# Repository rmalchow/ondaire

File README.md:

# ondaire

**Self-organizing multiroom audio.** One small binary per device. Start it on
two machines and they find each other, form a group, and play the same music
in sync — no server, no database, no config files, no cloud.

```
┌── kitchen ──┐   ┌── living room ──┐   ┌── bedroom ──┐
│  ondaire   │◀─▶│    ondaire     │◀─▶│  ondaire   │
└─────────────┘   └────────┬────────┘   └─────────────┘
                           │ plays a track from its library,
                           ▼ streams it in lock-step to the whole group
                     🔊  🔊  🔊   one song, every room, in time
```

- **Zero-config** — nodes discover each other over mDNS + gossip and replicate
  their state automatically. Pull the plug on any node and the rest heal.
- **One universal binary** — no cgo, no build flavors. Opus and ALSA are loaded
  at runtime if present, so the same `linux/amd64` or `linux/arm64` build runs
  on a beefy desktop or a Raspberry Pi.
- **Synchronized playback** — a master-anchored clock plus a per-node rate servo
  keep rooms aligned; lost packets are recovered with FEC or TCP.
- **Built-in web UI** — every node serves a single-page app at `/`. Control the
  whole cluster from any one of them.
- **Plays your stuff** — local files (`wav` / `mp3` / `flac`), internet radio
  (`http(s)://…`), or a line-in capture. Browse any node's library from any UI.
- **Group as you like** — any node is a group of one by default; tell one to
  follow another and they merge. Name a combination of rooms and the name
  sticks whenever that set reforms.

> A node can also be a receive-only **player**: the wire protocol is small and
> documented in [`docs/developer/player-protocol.md`](docs/developer/player-protocol.md) for firmware
> (e.g. an ESP32 + DAC), with a reference player in [`cmd/player`](cmd/player).

---

## Quick start

### Build

Needs Go 1.26 and Node (for the UI). Pure-Go, statically-ish linked:

```sh
git clone https://gitlab.rand0m.me/share/ondaire.git
cd ondaire
./scripts/build.sh --ui     # builds the SPA, then linux amd64 + arm64 into bin/,
                            # plus ./ondaire for this host
```

Prebuilt binaries are attached to each [tagged release](RELEASING.md).

**Running in Docker?** A multi-arch master image (amd64 + arm64, Spotify Connect
built in) plus a Compose example live in [`docker/`](docker/) — see the
[Docker quick start](QUICKSTART.md).

### Run

On each device:

```sh
./ondaire
```

That's it — defaults are sensible. The node mints a permanent ID on first run,
binds its ports, advertises itself over mDNS, and starts serving the UI. Run it
on a second machine on the same LAN and they find each other within seconds.

Open the UI in a browser:

```
http://<that-device's-ip>:8080
```

Put music in the node's library directory (created on first run):

```
<data-dir>/media/        # default: ./data/media — folders are browsed recursively
```

### Two nodes on one machine (to try it out)

```sh
./scripts/dev2.sh        # launches two nodes on 127.0.0.1 with null audio sinks
```

…or run the full end-to-end smoke test:

```sh
./scripts/e2e.sh
```

---

## Using the UI

Every node serves the same app and proxies to the others, so open
`http://<any-node-ip>:8080` on a phone or browser. There are two pages: the
**Rooms** overview (landing page) and the **Nodes** page (the **⚙ gear**,
top-right).

- **Rooms** — one card per group: now-playing (cover art / title / artist),
  group + per-member volumes, and — when you select a card — the add-players
  roster, the media browser, and advanced per-group settings (codec/transport/
  buffer).
- **Nodes** — per-node cards: addresses, feature toggles (playback/opus/input,
  plus a **spotify** badge), **Spotify endpoints** (Connect devices + presets),
  and settings (volume, hw delay, output device, test tone).

📖 **Full walkthrough with screenshots: [docs/user](docs/user/README.md).**

---

## Configuration

Flags (each has an `ONDAIRE_*` env equivalent); all are optional:

| Flag | Default | What |
|------|---------|------|
| `--data <dir>` | `./data` | data dir: `node.json`, `cluster.json`, `media/` |
| `--media <dir>` | `<data>/media` | library directory (browsed recursively) |
| `--name <name>` | first 8 of the node ID | display name (first start only) |
| `--http-port` | `8080` | UI + REST API + WebSocket + node proxy |
| `--stream-port` | `9090` | member-side stream + clock sync (tcp+udp) |
| `--source-port` | `9200` | audio source: subscriptions + control (tcp+udp) |
| `--gossip-port` | `7946` | cluster gossip (tcp+udp) |
| `--host <addr>` | all interfaces | bind address |
| `--output <spec>` | `auto` | output backend: `auto` \| `alsa` \| `exec` \| `null` \| `file:<path>` |

Ports are **bind-or-increment** *when left at the default*: if one is taken the
node tries the next and advertises whatever it actually bound. A port you **set
explicitly** (flag or `ONDAIRE_*_PORT` env) is **pinned** — it binds that exact
number or the node exits with a clear error, so a misconfiguration surfaces
immediately instead of silently drifting.

Env-only knobs:

| Env | Default | What |
|-----|---------|------|
| `ONDAIRE_ALSA_LATENCY_MS` | `200` | ALSA device buffer (raise on a glitchy Pi) |
| `ONDAIRE_LOG` | `info` | log level (`debug` \| `info` \| `warn` \| `error`) |

`auto` picks the best available backend: **alsa → exec** (`pw-play`/`aplay`/…)
**→ null**. Pass `-v` for debug logging; `ondaire run …` is accepted as an
alias for `ondaire …`.

For a hermetic setup without mDNS (e.g. tests, or a segmented network), use
`--no-mdns` with `--join <host:gossipPort>,…` seeds.

---

## How it works (in one breath)

Every node runs the identical binary and is, by default, the master of a group
containing only itself. Telling node B to *follow* node A merges them; the only
replicated fact is each node's `following` field — group membership, the group
ID (the master's ID), and failover all fall out of that, recomputed everywhere
from gossiped state. When a group plays, its master opens the media source,
stamps each 20 ms PCM/Opus frame with a presentation time on the shared clock,
and streams it to every member (including itself) that has *subscribed* to its
source port. Each member runs a clock follower and a jitter-buffered, rate-
servo'd playout so the audio leaves every speaker at the same instant.

Deeper docs live in [`docs/`](docs/), organized into four groups: the
[user guide](docs/user/), the [architecture reference](docs/architecture/)
(topic pages — wire protocol, clock sync, playout pipeline, sequence diagrams, …),
the [developer docs](docs/developer/) (the [player wire protocol](docs/developer/player-protocol.md),
the [ESP32 hardware node](docs/developer/esp32.md), and
[acoustic calibration](docs/developer/calibration.md)), and a
[reference section](docs/reference/) of external prior art.
[`RELEASING.md`](RELEASING.md) covers releases.

## Measured coherence

Sync is easy to claim, so we measured it. With a single USB microphone in the
room and two Raspberry-Pi players (`pi01` → left, `pi02` → right) we recorded the
real acoustic gap between the speakers over a 12-minute run.

**How it's measured.** Each speaker plays a wideband log-sine sweep, time-
interleaved L/R so the two never overlap. The recording is matched-filtered
against the reference sweep with sub-sample parabolic interpolation to pin each
arrival. The trick that makes it robust: every `pi02` sweep is referenced to the
**midpoint of its two bracketing `pi01` sweeps**, which cancels the (large,
common) playback-vs-microphone clock rate exactly and leaves only the
`pi01`↔`pi02` offset. As a ground-truth check, a deliberate ~50 cm speaker move
was recovered as 46 cm from the audio alone. The toolkit is pure Python in
[`tools/calib/`](tools/calib/) (`lr_drift.py`, `compare_drift.py`); the full
write-up is in [`docs/developer/calibration.md`](docs/developer/calibration.md).

### Inter-speaker offset: 716 µs RMS

The two speakers held to **716 µs RMS**, peak-to-peak ~2.7 ms. The curve is a
smooth thermal "bowl" (sound-card crystals warming up), not fast jitter. The
precedence/Haas effect fuses two arrivals into one perceived source up to ~5–10
ms, so this stays well inside the single-source range — sub-millisecond most of
the session, with a slow multi-ms thermal excursion the rate-servo doesn't cancel.

### What the servo can't see

Polling the master's per-node STATUS telemetry (`GET /api/playback/statuses`)
during the same run, the players' self-reported clock-offset difference stays
nearly flat while the microphone sees the full ~2.7 ms wander — correlation
**r = +0.20**. The drift lives **downstream of the clock the servo controls**, in
the DAC/analog path, where the chain is currently blind to it. That gap is small
enough to be inaudible, but it's exactly what on-demand acoustic calibration
(`outputDelayMs`) is designed to measure and null.

## Status & scope

Works today: discovery, grouping, takeover, synchronized playback, pause/resume,
opus, per-node volume/delay/device, persisted names & settings, the web UI, and
a tag-driven release pipeline. Out of scope for now: auth/TLS, internet-facing
operation, playlists, and hardware-mixer volume. v1 is a trusted-LAN system.

## On AI

Yes — I used Claude for much of this code. No, it isn't vibe-coded AI slop. The
architecture, the clock-sync math, the wire protocol, and the trade-offs behind
every design decision are my own thinking and experience, and I know and
understand pretty much every line that ships. I used AI the way you'd use any
good power tool: to get past my own laziness and move faster, not to outsource
the judgement. If something in here is wrong, that's on me, not on a model.

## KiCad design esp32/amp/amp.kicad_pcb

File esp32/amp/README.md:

# ondaire amp — ESP32-S3 carrier / 50 W class-D node

A KiCad 10 project for a **powered-speaker node**: an ESP32-S3 dev board drops
into a socket, an I²S DAC + class-D amp turn the stream into ~40–50 W of audio,
and the whole thing runs from a single USB-C cable via USB-PD. JST plugs bring
out a rotary encoder and an I²C OLED.

This carrier is the hardware counterpart to the `esp32/` firmware in this repo —
the GPIO map, I²S pins and encoder pins are taken straight from
`esp32/boards/board_esp32s3_*.h`, so a flashed Super Mini or Waveshare Zero
works with no reconfiguration.

> **Status — schematic ERC-clean; board placed + ground-poured, not yet routed.**
> Schematic, symbols, footprints, BOM and netlist are generated and validated
> (`kicad-cli sch erc` → 0 errors). The `.kicad_pcb` has every footprint placed
> in a functional floorplan with GND zones on both layers; DRC is clean except
> the expected unrouted ratsnest (no overlaps/clearance/short errors). **Signal
> and power routing is the remaining manual step.** A few values need a
> datasheet/board check before you order — see
> [Verify before you order](#verify-before-you-order).

---

## Block diagram

```
            ┌───────── USB-C (PD) ─────────┐
   charger  │  VBUS ─┬─────────────► +20V rail ──────────────┐
   ─────────┤  CC1/2─┤ CH224K       (≈3 A @ 20 V)            │
   20V/65W+ │  D±  ───┘ PD sink                              │
            └─────────┘  (CFG1: NC = request 20 V)           │
                                                             │
          +20V ──► LM2596S-5.0 buck ──► +5V ──► AMS1117-3.3 ──► +3V3
                                         │                      │
                                         ▼                      ▼
                                   ESP32-S3 socket        PCM5102A DAC
                                   (Super Mini / Zero)    (MCLK-less I²S)
                                         │  I²S BCK/LRCK/DIN     │
                                         └──────────────────────┘
                                                                │ OUT L/R
                                       L+R passive sum ◄─────────┘
                                                │
                          +20V ──► TPA3116D2 (PBTL mono) ──► LC filter ──► SPEAKER
                                       ▲   ▲                              (4 Ω, ~50 W)
                                  SD/FAULT  gain=20 dB
                                       │
   JST: OLED (I²C SDA/SCL) ────────────┤ ESP32 GPIO
   JST: rotary encoder (A/B/SW) ───────┘
```

## What was decided

| Choice | Decision | Why |
|---|---|---|
| Amp topology | **TPA3116D2, mono PBTL** | One speaker per node; PBTL gives ~40–50 W into 4 Ω from a 20 V rail (min load 1.6 Ω). |
| DAC | **PCM5102A**, MCLK-less | Matches the firmware (`i2s_mclk = -1`, internal PLL); clean 2.1 Vrms line out, no I²C config. |
| Power | **USB-PD 20 V via CH224K** | Single-cable power; 20 V is the TPA3116's sweet spot. Single-resistor select, default = 20 V. |
| ESP socket | **Both Super Mini + Zero** | Populate one footprint; identical nets, so one board fits either dev board. |
| Buck / LDO | LM2596S-5.0 → AMS1117-3.3 | 20 V is above most synchronous bucks' input max; LM2596 (40 V in) is robust. Separate clean 3V3 for the DAC. |

## Signal & power chain (the important bits)

**USB-PD (CH224K).** USB-C VBUS feeds the +20 V rail directly; the CH224K only
negotiates. Voltage is set in *single-resistor* mode: **R1 on CFG1→GND, with
CFG2/CFG3 unconnected.** R1 **unpopulated = 20 V**; 6.8 k = 9 V, 24 k = 12 V,
56 k = 15 V (WCH CH224K DS §5.2.1). D± route to the CH224K for BC1.2 fallback.

**Amp (TPA3116D2 PBTL).** Wired per the TI datasheet mono mode (SLOS708G §7.4.1,
Fig. 36):
- `LINP`, `LINN` → GND (this selects PBTL/mono at power-up).
- Signal into `RINP`/`RINN` (single-ended L+R sum, AC-coupled).
- Outputs paralleled: **`OUTPR ∥ OUTNR` → SPK+**, **`OUTPL ∥ OUTNL` → SPK−**,
  each half-bridge through its own 10 µH inductor, 1 µF across the speaker
  (PBTL filter, min L = 10 µH / C = 1 µF).
- `MODSEL` = GND (BD modulation, lowest THD with the LC filter).
- `PLIMIT` tied to `GVDD` (no power limit). `GAIN/SLV` = 5.6 k to GVDD → **20 dB,
  master mode** (lowest gain the part offers).
- `SDZ` (enable) ← ESP GPIO1 with a 100 k pull-down (amp stays off at boot).
  `FAULTZ` → GPIO4 (10 k pull-up). `MUTE` tied low (software volume handles mute).
- All four `BSxx` bootstrap caps = 220 nF. `AVCC` fed from +20 V through a 3.3 Ω
  RC. PowerPAD → GND (thermal vias).

**Gain / headroom.** At 20 dB the PCM5102A's 2.1 Vrms full-scale over-drives the
20 V rail by a few dB, so the **firmware's digital volume sets the real level** —
keep it below ~−4 dBFS for clean full power (normal listening is well under that).
To hard-limit in hardware, populate **R17** (MIXIN→GND, DNP) to attenuate/divide
the summer.

## GPIO map (matches `esp32/boards/board_esp32s3_*.h`)

| Signal | GPIO | Notes |
|---|---|---|
| I²S BCK | 5 | → PCM5102A BCK |
| I²S LRCK | 6 | → PCM5102A LCK |
| I²S DIN | 7 | → PCM5102A DIN (MCLK-less; SCK→GND) |
| Encoder A / B / SW | 15 / 16 / 17 | KY-040 / EC11 via JST (J4) |
| I²C SDA / SCL | 8 / 18 | SSD1306 OLED via JST (J3) |
| Amp enable (SDZ) | 1 | **new** — drive high to un-shutdown the amp |
| CH224K PG | 2 | **new** — power-good input |
| Amp FAULTZ | 4 | **new** — fault input (open-drain) |

GPIO 1/2/4/8/18 are the carrier-only additions; they're free and conflict-free on
both boards. The firmware doesn't drive amp-enable / fault / OLED yet — the board
is forward-looking on those. (3V3 from the dev board is left unconnected; the
carrier makes its own clean 3V3 for the DAC.)

## Power budget

| Rail | Source | Load | Worst-case |
|---|---|---|---|
| +20 V | USB-PD | TPA3116 PVCC | ~3 A at full output |
| +5 V | LM2596S-5.0 | ESP32 (Wi-Fi TX peaks) + LDO | ~1 A |
| +3V3 | AMS1117-3.3 | DAC + OLED + pull-ups | ~50 mA |

Full output (~50 W audio, ~90 % amp efficiency) + logic ≈ **60 W** → use a
**≥ 65 W (20 V / 3.25 A) charger**; a 100 W (20 V/5 A) supply gives headroom.
A 60 W (20 V/3 A) charger works but limits peak SPL.

## Files

| File | What |
|---|---|
| `amp.kicad_pro` | Project. Open this in KiCad 10. |
| `amp.kicad_sch` | Schematic (generated). |
| `amp.kicad_pcb` | Board: placed + GND-poured, unrouted (generated). |
| `amp.kicad_sym` | Project symbols: TPA3116D2 + the two ESP32 sockets (generated). |
| `amp.pretty/` | Project footprints: ESP32 dev-board sockets (generated, **placeholder geometry**). |
| `sym-lib-table`, `fp-lib-table` | Register the `amp` libs for this project. |
| `bom.csv` | Grouped BOM with LCSC starting points (generated). |
| `gen_*.py`, `ksym.py` | The generators — **edit these, not the outputs.** |

### Regenerating

The schematic/symbols/footprints/BOM are produced from declarative data so the
design is diffable and editable. After changing `gen_sch.py` (netlist/parts):

```sh
cd esp32/amp
python3 gen_symbols.py      # amp.kicad_sym
python3 gen_footprints.py   # amp.pretty/*
python3 gen_sch.py          # amp.kicad_sch
python3 gen_bom.py          # bom.csv
python3 gen_pcb.py          # amp.kicad_pcb (needs KiCad's pcbnew python module)
kicad-cli sch erc amp.kicad_sch   # validate schematic
kicad-cli pcb drc amp.kicad_pcb   # validate board
```

The schematic is a **connectivity-capture** style: components on a grid with a
global label on every pin (same name = same net). It's ERC-clean and exports a
correct netlist; tidy the layout/wiring in Eeschema if you want a pretty sheet.

## PCB layout

`gen_pcb.py` builds the board with the `pcbnew` API: it reads each footprint's
real courtyard size and shelf-packs the parts into functional regions (power-in
+ PD top-left, buck/LDO across the top, DAC upper-right, amp + output filter +
speaker lower-right, sockets + user-IO on the left), then pours **GND on both
copper layers**. The TPA3116 uses the `_ThermalVias` footprint, so its PowerPAD
is already stitched to the back plane.

What's left for you (in Pcbnew):

1. **Fill zones** — they're saved unfilled (a headless-`pcbnew` limitation);
   press `B` or *Edit → Fill All Zones* on open. This connects the whole GND net.
2. **Route** the ~46 non-GND nets. Suggested priorities:
   - Wide tracks for **+20V** and the **speaker outputs** (≥1.5 mm; ~3.5 A) and
     the buck **+5V** path; keep the buck's SW node / catch-diode loop tight.
   - Keep the four **TPA3116 output → inductor → speaker** runs short and
     symmetric; the LC filter and bulk PVCC caps right at the amp.
   - **I²S** (BCK/LRCK/DIN) short from socket to DAC; star the DAC analog ground.
3. **Finalize the ESP32 socket land patterns** (placeholders — see below) and add
   a mechanical support header on the board's far edge.
4. Re-run DRC. The generated board is DRC-clean apart from the unrouted ratsnest
   (no overlap/clearance/short errors) and a couple of cosmetic silk-over-pad
   warnings; 2-layer works, **4-layer is recommended** for a quiet ground plane
   under the amp.

> The placement is a *starting point* — nudge parts to suit your routing. Re-running
> `gen_pcb.py` overwrites `amp.kicad_pcb`, so once you start routing by hand, stop
> regenerating it (keep editing the schematic + re-import instead).

## Assembly (Aisler)

Designed to be SMT-assemblable. All ICs and passives are SMD (0805 jellybean,
HTSSOP/TSSOP/SOT/TO-263). **Hand-soldered (not SMT-placed):** the ESP32 socket
headers, the JST plugs, and the speaker terminal block — Aisler does SMT
assembly, so place these THT parts yourself.

- 2-layer is workable; **prefer 4-layer** for a solid ground plane under the amp.
- Footprints use Aisler/JLC-friendly packages; LCSC codes in `bom.csv` are
  *starting points* — verify against the live catalogue.
- For the TPA3116 PowerPAD, keep the thermal-via footprint variant (it's the one
  assigned) and pour ground top+bottom.

## Verify before you order

These are flagged in the BOM / netlist and need a quick check against your parts:

1. **ESP32 socket footprints** (`amp.pretty/*`) are **placeholders** — 1×14
   headers tapping the GPIO1–18 edge. Super Mini clones vary in length / row
   spacing, and the Zero is castellated+THT. **Measure your actual board** and
   redraw the land pattern (and add a mechanical support header on the far edge).
   Pad numbers already match the symbol, so the netlist survives the edit.
2. **CH224K footprint** — ESSOP-10; confirm the MSOP-10-1EP land matches your
   exact part marking.
3. **Output inductors** — `L_12x12mm_H6mm` placeholder; pick 10 µH parts rated
   **≥ 4 A saturation** (e.g. shielded power inductors), 33 µH ≥ 3 A for the buck.
4. **Electrolytics** — `CP_Elec_8x10.5` placeholder; match diameter/pitch to the
   470 µF/35 V and 220–330 µF parts you actually buy.
5. **Amp gain** (R9) and **AM switching-frequency** pins (AM0/1/2 → GND default)
   per the TPA3116 datasheet if you want something other than 20 dB / default fsw.

## References

- TI TPA3116D2 datasheet (SLOS708G) — pinout, PBTL mono (§7.4.1), filters.
- WCH CH224K datasheet — single-resistor voltage select (§5.2.1).
- TI PCM5102A datasheet — MCLK-less / internal-PLL operation.
- `esp32/boards/board_esp32s3_*.h` — the firmware's GPIO truth.

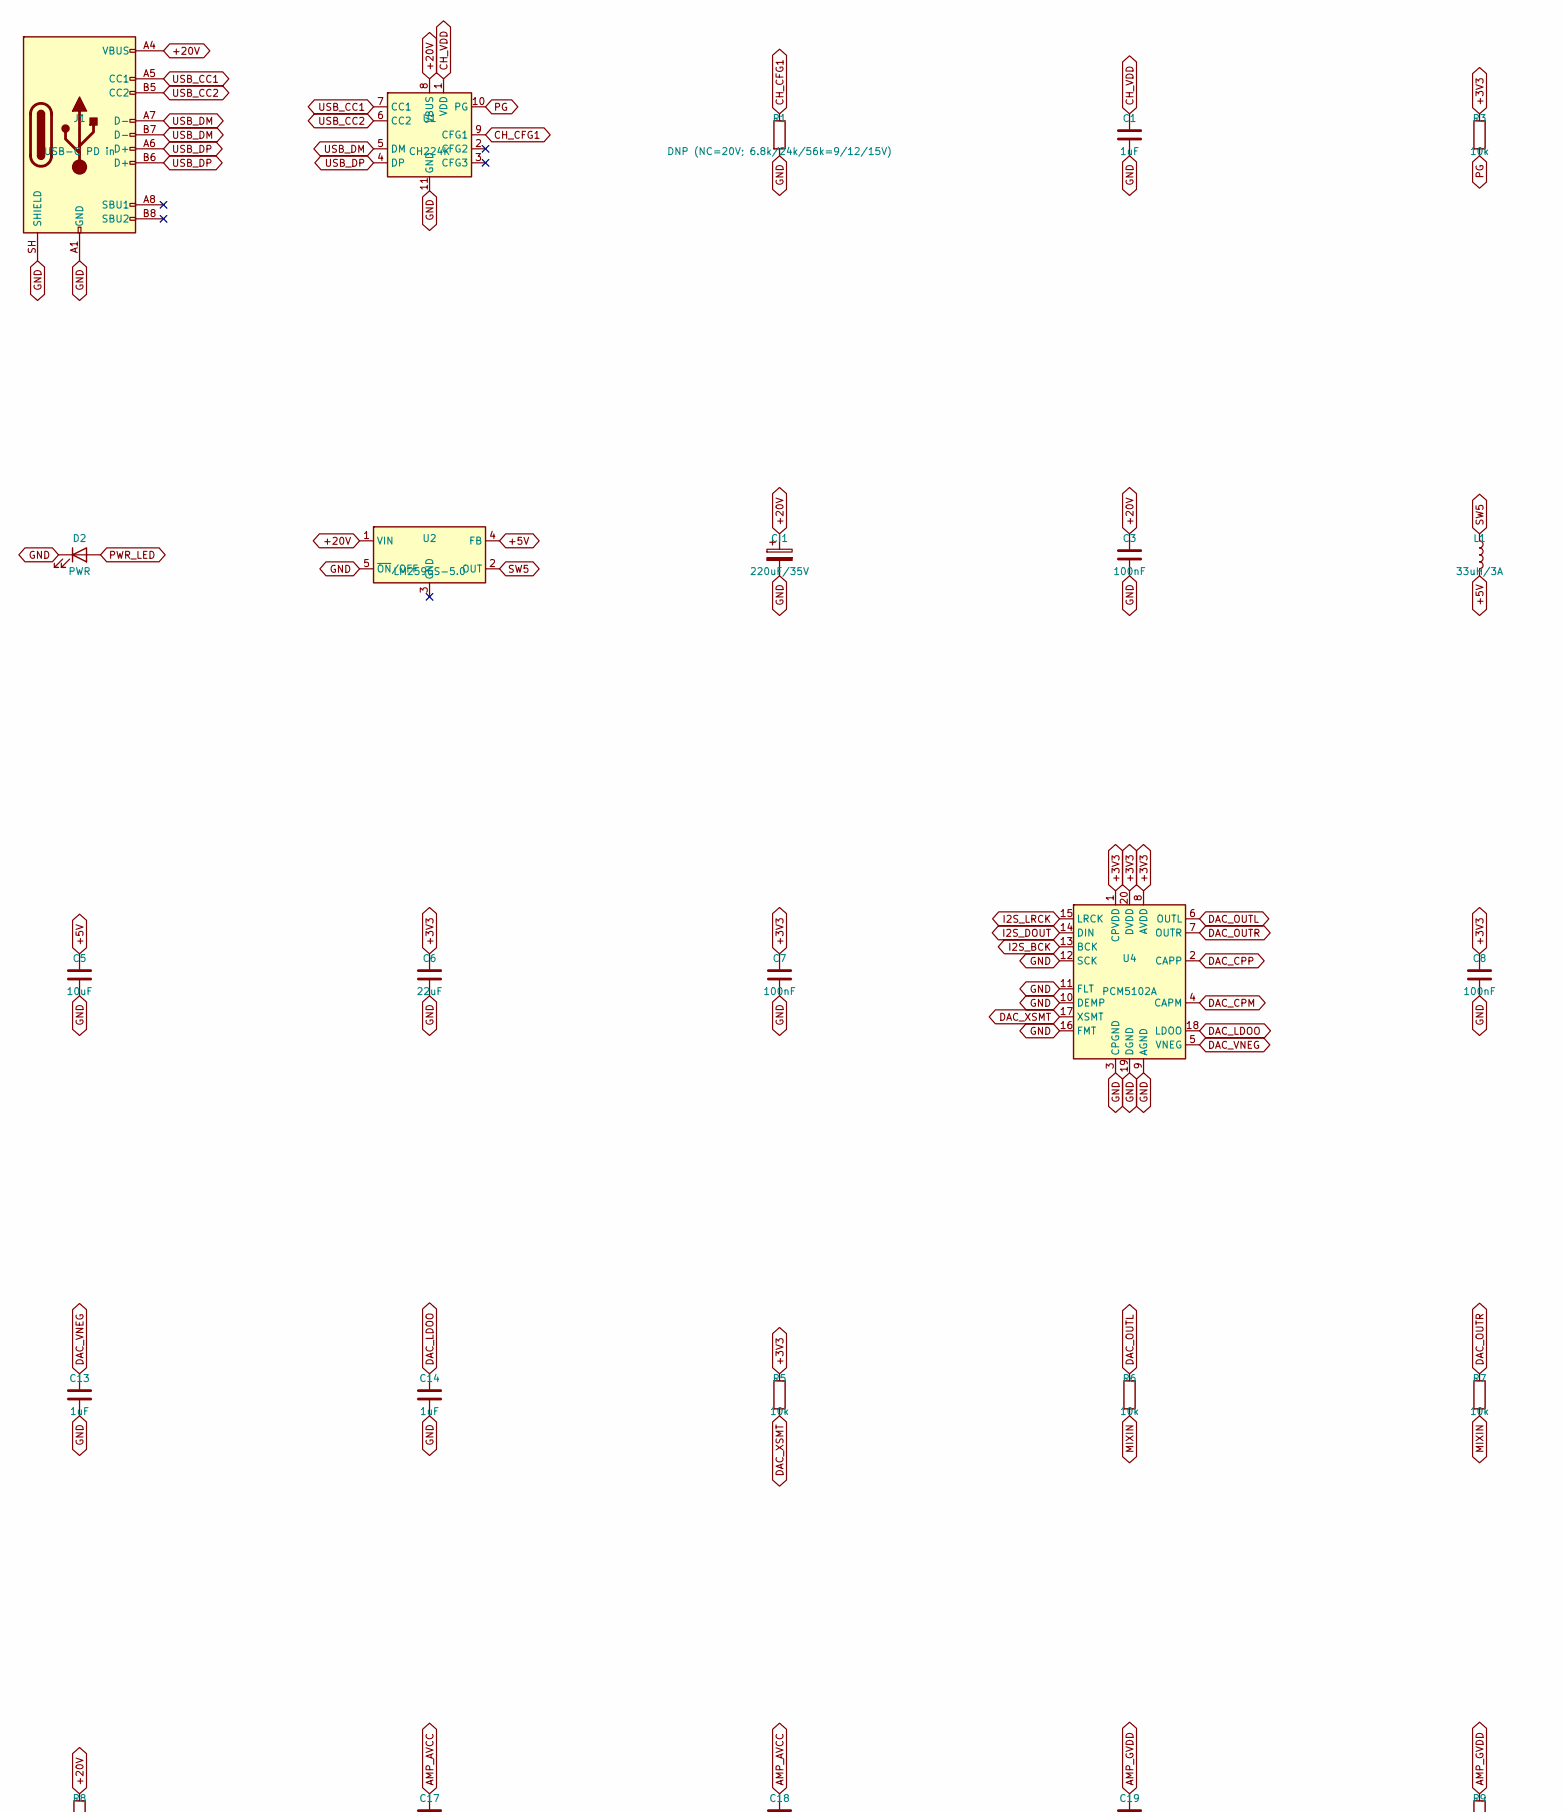
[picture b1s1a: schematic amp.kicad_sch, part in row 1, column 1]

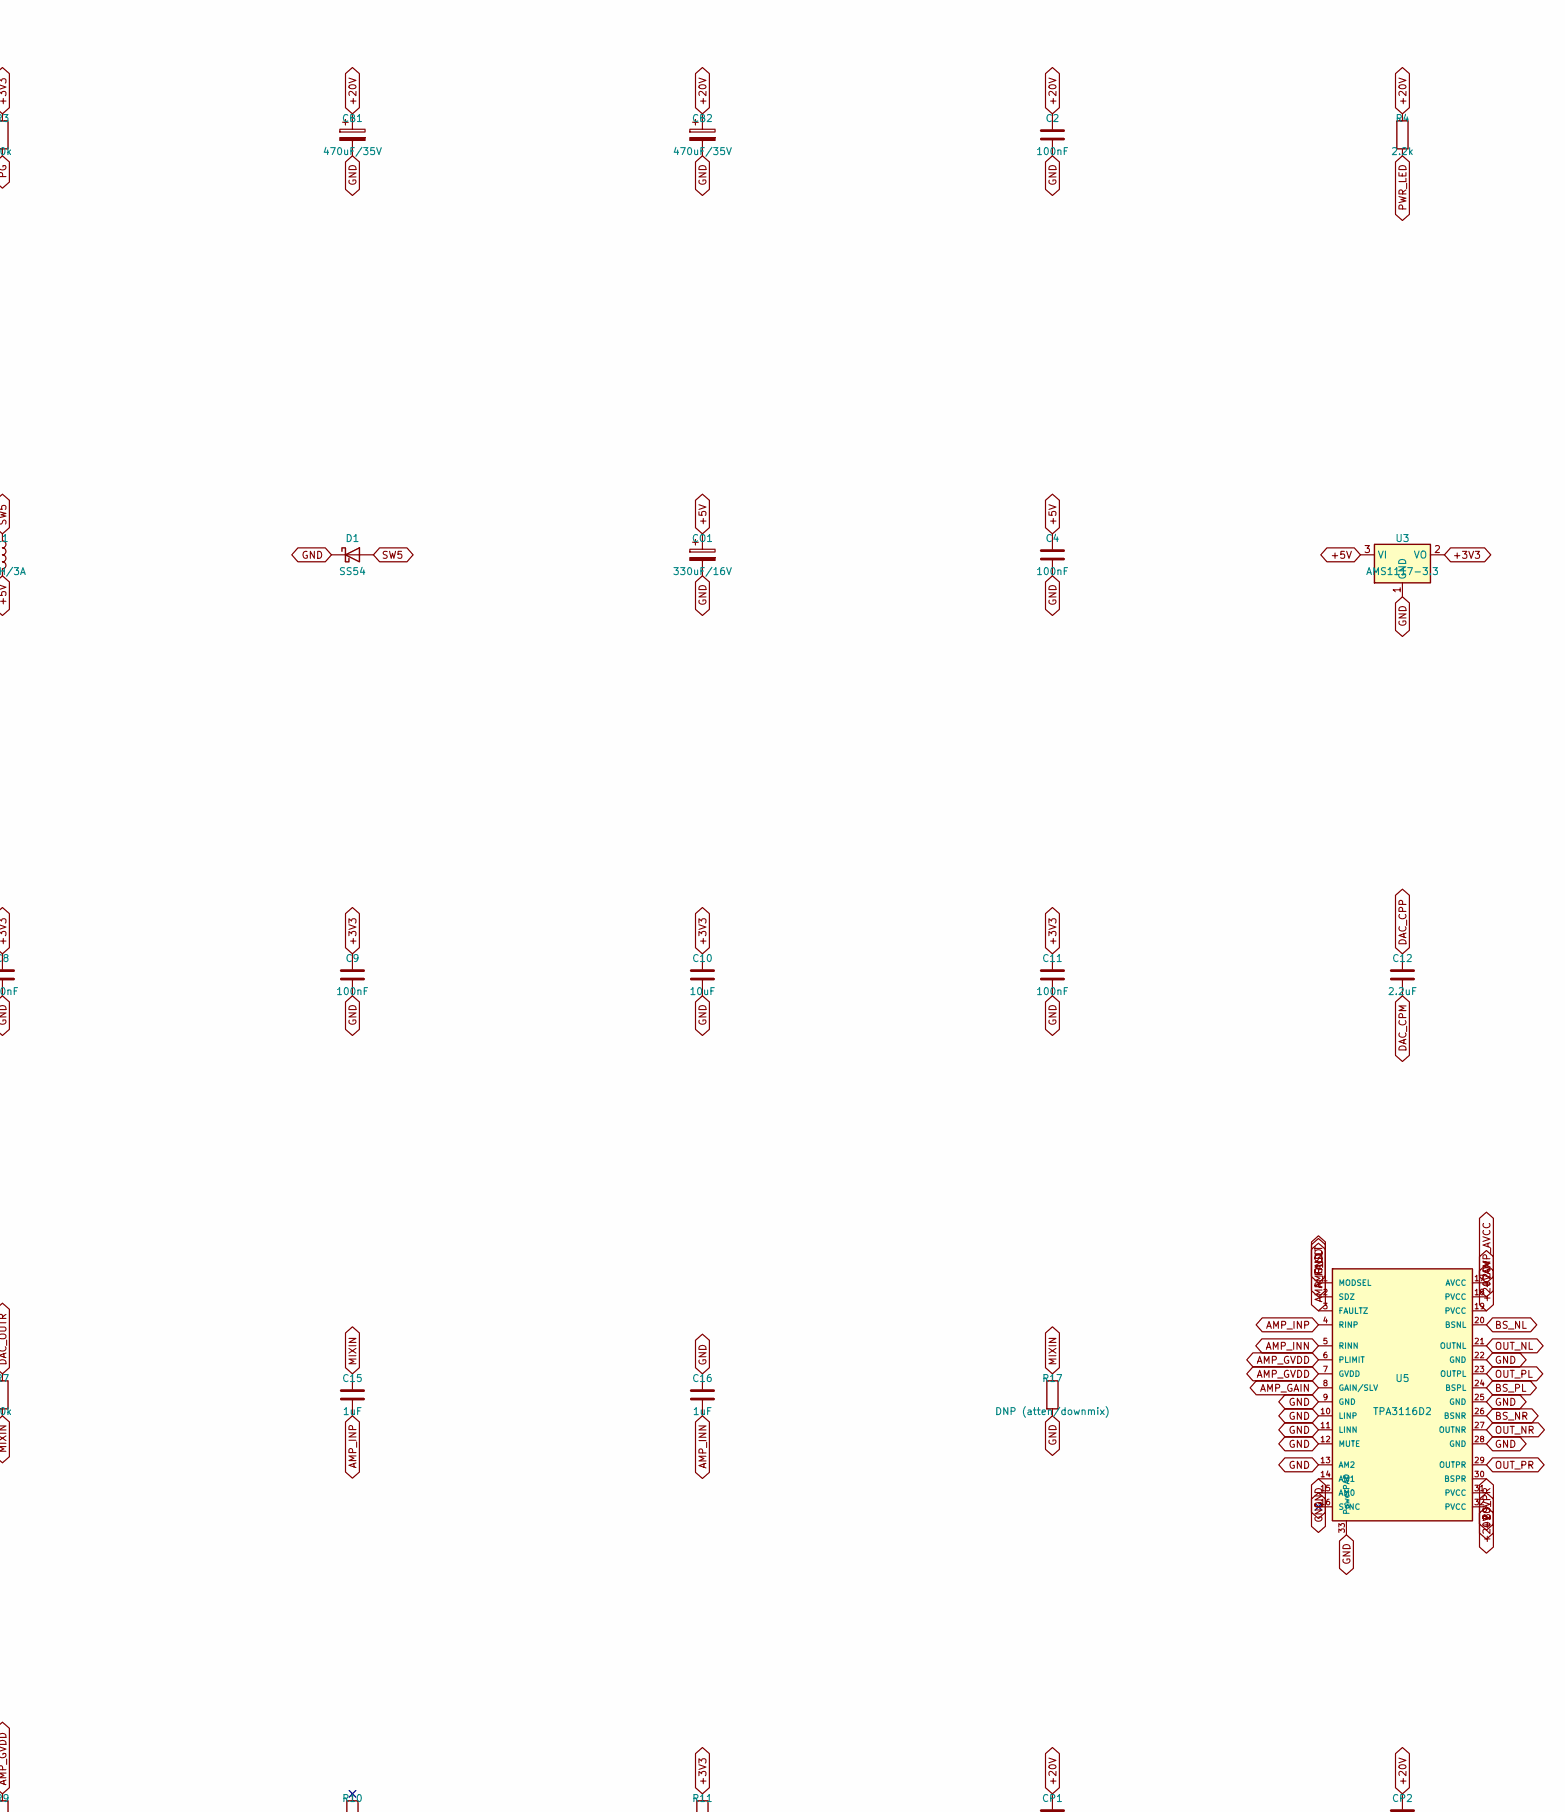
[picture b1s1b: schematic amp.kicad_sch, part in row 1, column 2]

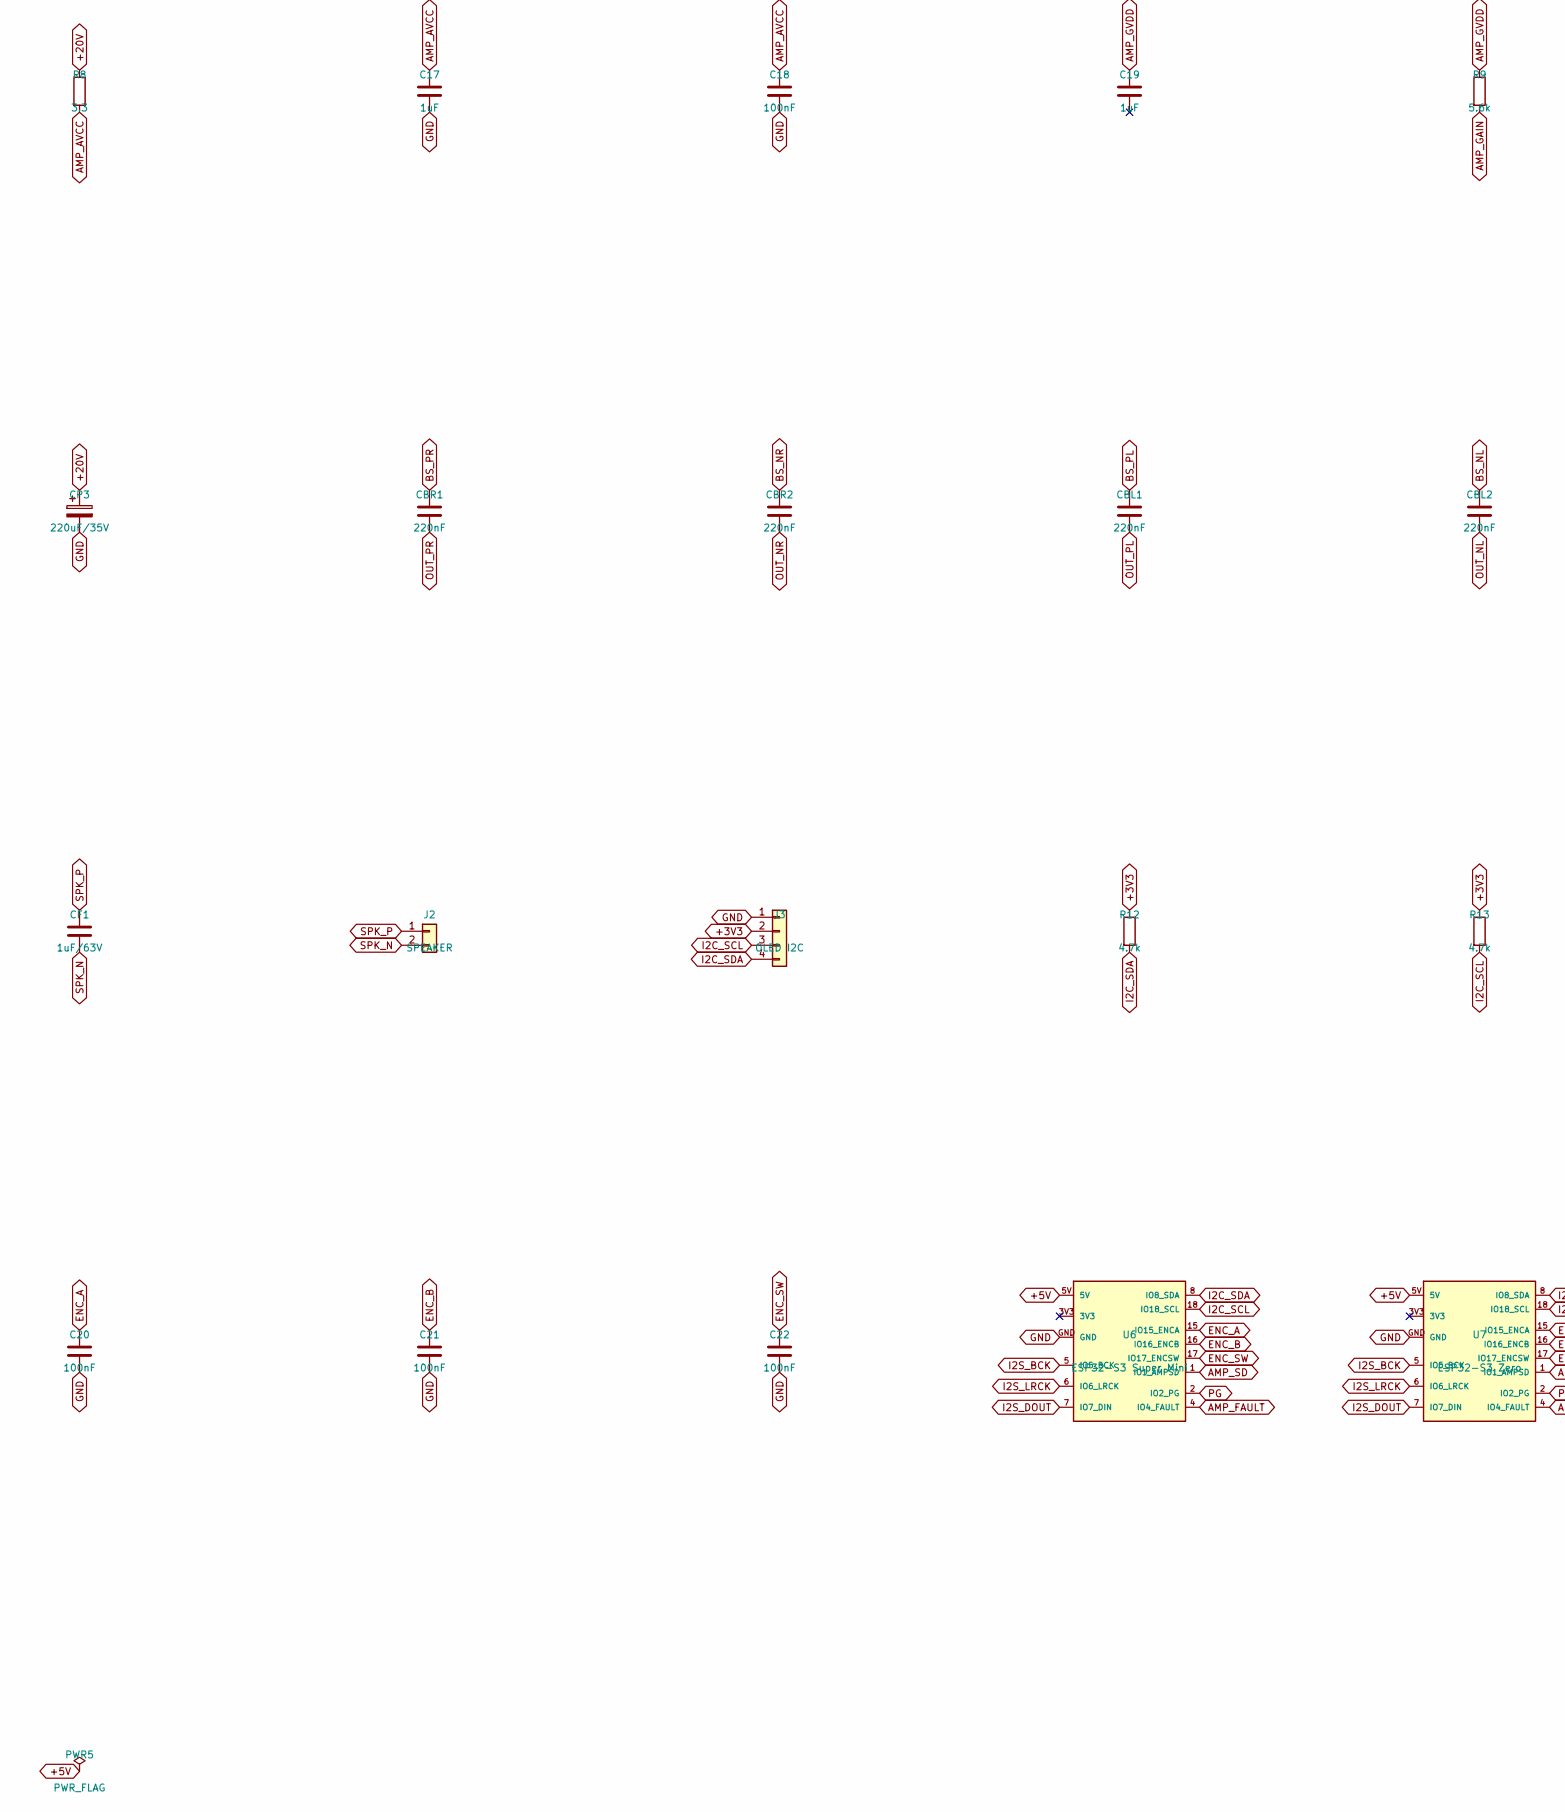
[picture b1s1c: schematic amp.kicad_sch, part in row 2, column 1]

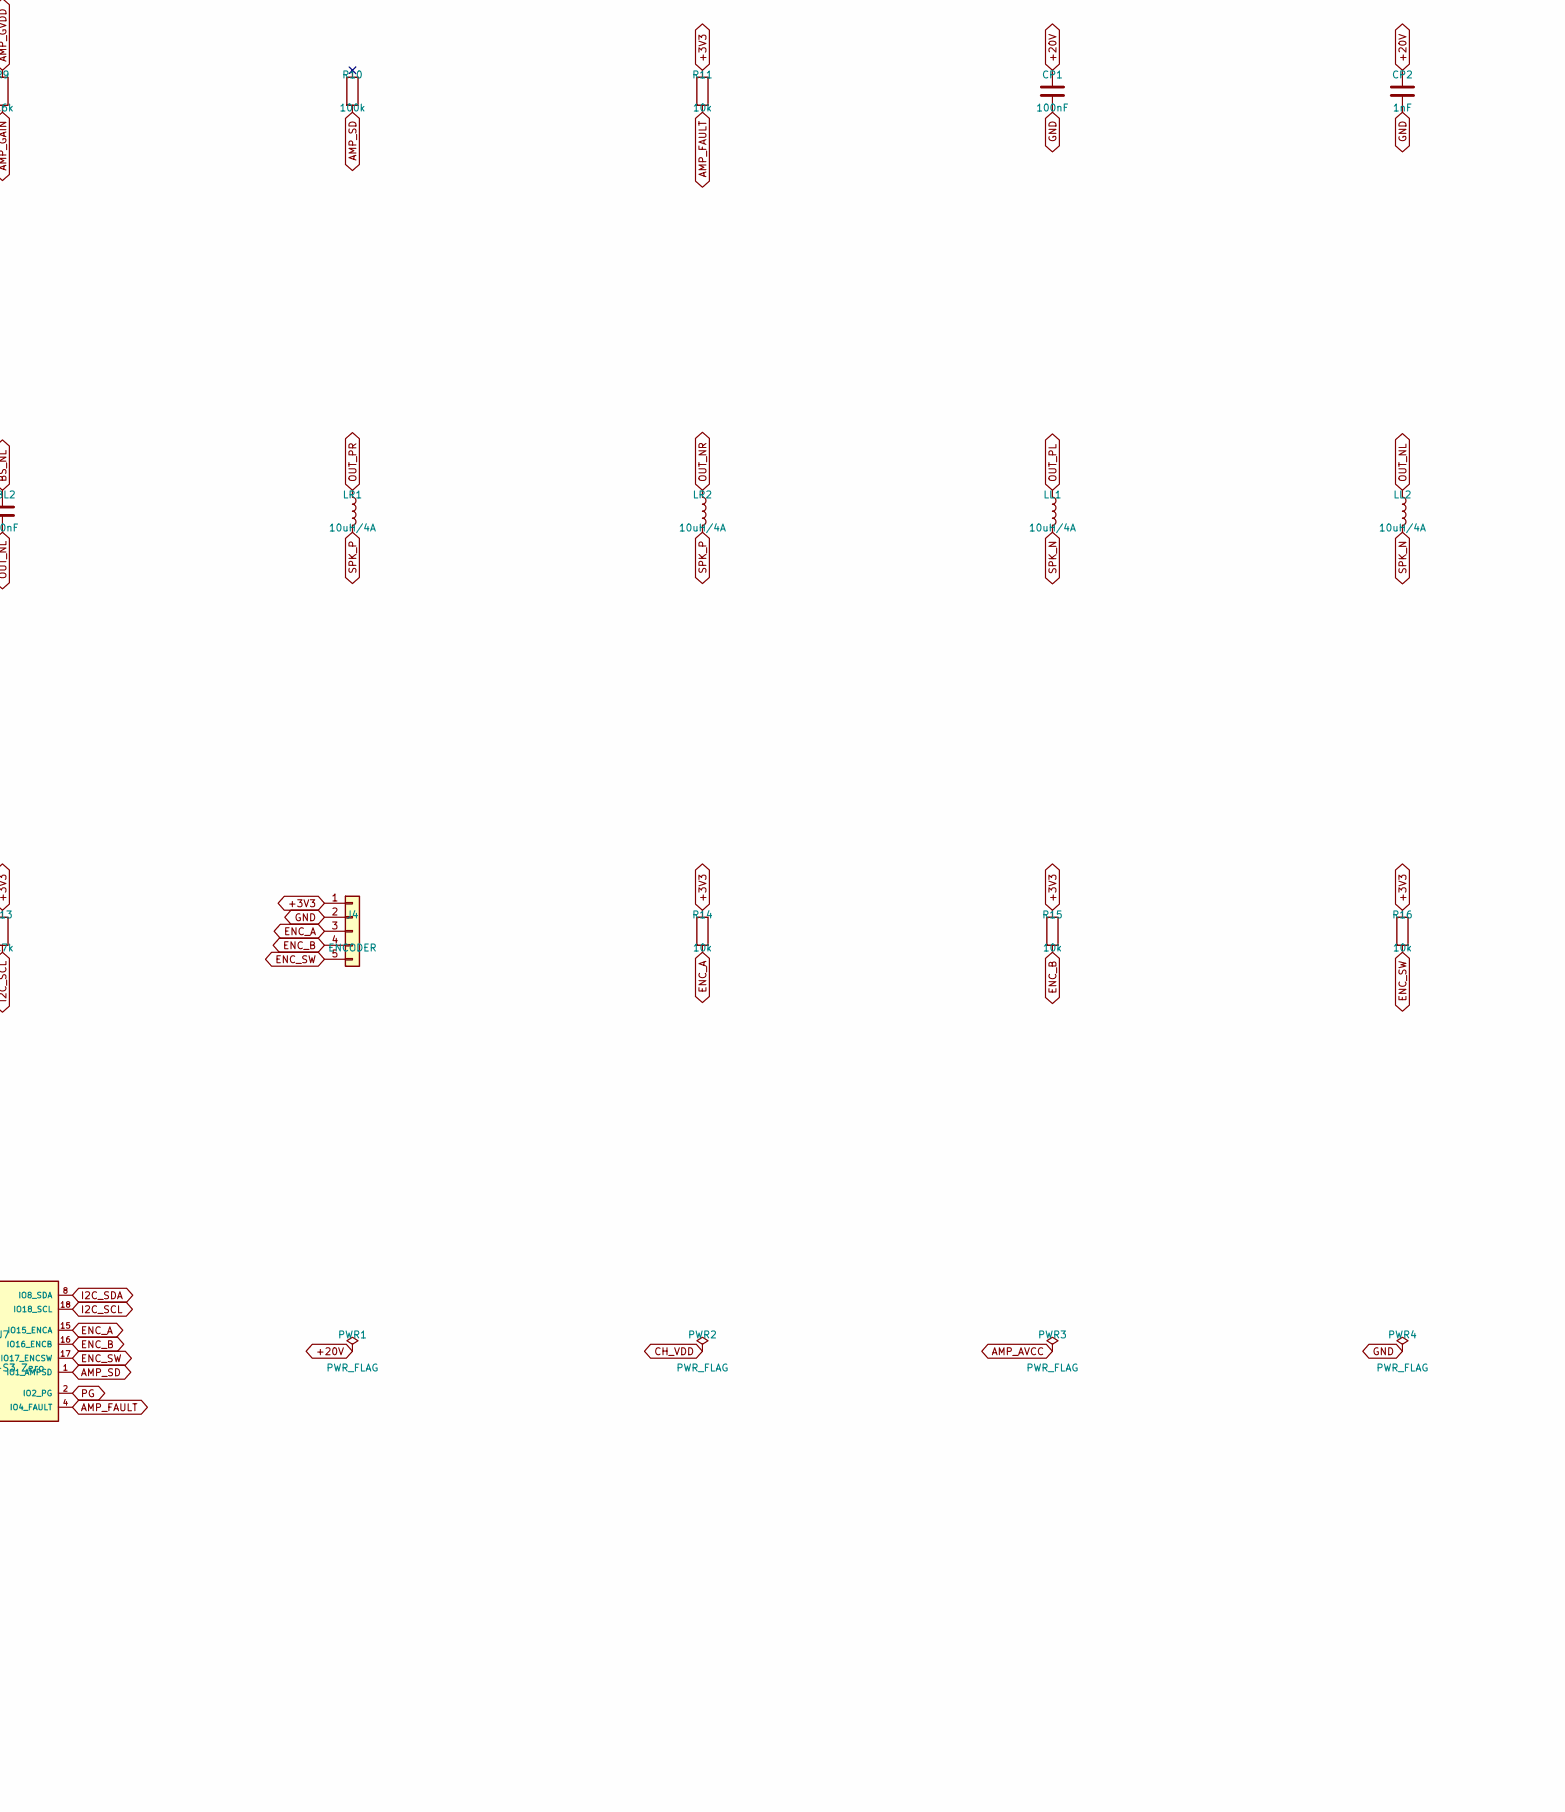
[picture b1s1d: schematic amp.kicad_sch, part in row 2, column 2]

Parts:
C1, C13, C14, C15, C16, C17, C19: 1uF; C_0805_2012Metric
C2, C3, C4, C7, C8, C9, C11, C18, C20, C21, C22: 100nF; C_0805_2012Metric
C5, C10: 10uF; C_0805_2012Metric
C6: 22uF; C_0805_2012Metric
C12: 2.2uF; C_0805_2012Metric
CB1, CB2: 470uF/35V; CP_Elec_8x10.5
CBL1, CBL2: 220nF; C_0805_2012Metric
CBR1, CBR2: 220nF; C_0805_2012Metric
CF1: 1uF/63V; C_0805_2012Metric
CI1: 220uF/35V; CP_Elec_8x10.5
CO1: 330uF/16V; CP_Elec_8x10.5
CP1: 100nF; C_0805_2012Metric
CP2: 1nF; C_0805_2012Metric
CP3: 220uF/35V; CP_Elec_8x10.5
D1: SS54; D_SMB
D2: PWR; LED_0805_2012Metric
J1: USB-C PD in; USB_C_Receptacle_GCT_USB4085
J2: SPEAKER; TerminalBlock_Phoenix_MKDS-1,5-2_1x02_P5.00mm_Horizontal
J3: OLED I2C; JST_PH_B4B-PH-K_1x04_P2.00mm_Vertical
J4: ENCODER; JST_PH_B5B-PH-K_1x05_P2.00mm_Vertical
L1: 33uH/3A; L_12x12mm_H6mm
LL1, LL2: 10uH/4A; L_7.3x7.3_H4.5
LR1, LR2: 10uH/4A; L_7.3x7.3_H4.5
PWR1, PWR2, PWR3, PWR4, PWR5: PWR_FLAG
R1: DNP (NC=20V; 6.8k/24k/56k=9/12/15V); R_0805_2012Metric
R3, R5, R6, R7, R11, R14, R15, R16: 10k; R_0805_2012Metric
R4: 2.2k; R_0805_2012Metric
R8: 3.3; R_0805_2012Metric
R9: 5.6k; R_0805_2012Metric
R10: 100k; R_0805_2012Metric
R12, R13: 4.7k; R_0805_2012Metric
R17: DNP (atten/downmix); R_0805_2012Metric
U1: CH224K; MSOP-10-1EP_3x3mm_P0.5mm_EP1.73x1.98mm
U2: LM2596S-5.0; TO-263-5_TabPin3
U3: AMS1117-3.3; SOT-223-3_TabPin2
U4: PCM5102A; TSSOP-20_4.4x6.5mm_P0.65mm
U5: TPA3116D2; HTSSOP-32-1EP_6.1x11mm_P0.65mm_EP5.2x11mm_Mask4.11x4.36mm_T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
U6: ESP32-S3 Super Mini; ESP32S3_SuperMini_Socket
U7: ESP32-S3 Zero; ESP32S3_Zero_Socket

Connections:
+3V3: C6.1, C7.1, C8.1, C9.1, C10.1, C11.1, J3.2, J4.1, R3.1, R5.1, R11.1, R12.1, R13.1, R14.1, R15.1, R16.1, U3.2 (VO), U4.1 (CPVDD), U4.8 (AVDD), U4.20 (DVDD)
+5V: C4.1, C5.1, CO1.1, L1.2, PWR5.1, U2.4 (FB), U3.3 (VI), U6.5V, U7.5V
+20V: C2.1, C3.1, CB1.1, CB2.1, CI1.1, CP1.1, CP2.1, CP3.1, J1.A4 (VBUS), J1.A9 (VBUS), J1.B4 (VBUS), J1.B9 (VBUS), PWR1.1, R4.1, R8.1, U1.8 (VBUS), U2.1 (VIN), U5.18 (PVCC), U5.19 (PVCC), U5.31 (PVCC), U5.32 (PVCC)
AMP_AVCC: C17.1, C18.1, PWR3.1, R8.2, U5.17 (AVCC)
AMP_FAULT: R11.2, U5.3 (FAULTZ), U6.4 (IO4_FAULT), U7.4 (IO4_FAULT)
AMP_GAIN: R9.2, U5.8 (GAIN/SLV)
AMP_GVDD: C19.1, R9.1, U5.6 (PLIMIT), U5.7 (GVDD)
AMP_INN: C16.2, U5.5 (RINN)
AMP_INP: C15.2, U5.4 (RINP)
AMP_SD: R10.2, U5.2 (SDZ), U6.1 (IO1_AMPSD), U7.1 (IO1_AMPSD)
BS_NL: CBL2.1, U5.20 (BSNL)
BS_NR: CBR2.1, U5.26 (BSNR)
BS_PL: CBL1.1, U5.24 (BSPL)
BS_PR: CBR1.1, U5.30 (BSPR)
CH_CFG1: R1.1, U1.9 (CFG1)
CH_VDD: C1.1, PWR2.1, U1.1 (VDD)
DAC_CPM: C12.2, U4.4 (CAPM)
DAC_CPP: C12.1, U4.2 (CAPP)
DAC_LDOO: C14.1, U4.18 (LDOO)
DAC_OUTL: R6.1, U4.6 (OUTL)
DAC_OUTR: R7.1, U4.7 (OUTR)
DAC_VNEG: C13.1, U4.5 (VNEG)
DAC_XSMT: R5.2, U4.17 (XSMT)
ENC_A: C20.1, J4.3, R14.2, U6.15 (IO15_ENCA), U7.15 (IO15_ENCA)
ENC_B: C21.1, J4.4, R15.2, U6.16 (IO16_ENCB), U7.16 (IO16_ENCB)
ENC_SW: C22.1, J4.5, R16.2, U6.17 (IO17_ENCSW), U7.17 (IO17_ENCSW)
GND: C1.2, C2.2, C3.2, C4.2, C5.2, C6.2, C7.2, C8.2, C9.2, C10.2, C11.2, C13.2, C14.2, C16.1, C17.2, C18.2, C20.2, C21.2, C22.2, CB1.2, CB2.2, CI1.2, CO1.2, CP1.2, CP2.2, CP3.2, D1.1 (K), D2.1 (K), J1.A1 (GND), J1.A12 (GND), J1.B1 (GND), J1.B12 (GND), J1.SH (SHIELD), J3.1, J4.2, PWR4.1, R1.2, R17.2, U1.11 (GND), U2.5 (~ON/OFF), U3.1 (GND), U4.3 (CPGND), U4.9 (AGND), U4.10 (DEMP), U4.11 (FLT), U4.12 (SCK), U4.16 (FMT), U4.19 (DGND), U5.1 (MODSEL), U5.9 (GND), U5.10 (LINP), U5.11 (LINN), U5.12 (MUTE), U5.13 (AM2), U5.14 (AM1), U5.15 (AM0), U5.22 (GND), U5.25 (GND), U5.28 (GND), U5.33 (PowerPAD), U6.GND, U7.GND
I2C_SCL: J3.3, R13.2, U6.18 (IO18_SCL), U7.18 (IO18_SCL)
I2C_SDA: J3.4, R12.2, U6.8 (IO8_SDA), U7.8 (IO8_SDA)
I2S_BCK: U4.13 (BCK), U6.5 (IO5_BCK), U7.5 (IO5_BCK)
I2S_DOUT: U4.14 (DIN), U6.7 (IO7_DIN), U7.7 (IO7_DIN)
I2S_LRCK: U4.15 (LRCK), U6.6 (IO6_LRCK), U7.6 (IO6_LRCK)
MIXIN: C15.1, R6.2, R7.2, R17.1
OUT_NL: CBL2.2, LL2.1, U5.21 (OUTNL)
OUT_NR: CBR2.2, LR2.1, U5.27 (OUTNR)
OUT_PL: CBL1.2, LL1.1, U5.23 (OUTPL)
OUT_PR: CBR1.2, LR1.1, U5.29 (OUTPR)
PG: R3.2, U1.10 (PG), U6.2 (IO2_PG), U7.2 (IO2_PG)
PWR_LED: D2.2 (A), R4.2
SPK_N: CF1.2, J2.2, LL1.2, LL2.2
SPK_P: CF1.1, J2.1, LR1.2, LR2.2
SW5: D1.2 (A), L1.1, U2.2 (OUT)
USB_CC1: J1.A5 (CC1), U1.7 (CC1)
USB_CC2: J1.B5 (CC2), U1.6 (CC2)
USB_DM: J1.A7 (D-), J1.B7 (D-), U1.5 (DM)
USB_DP: J1.A6 (D+), J1.B6 (D+), U1.4 (DP)

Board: 2 copper layers, 68 parts (0 on the bottom side), 46 nets, no tracks yet.

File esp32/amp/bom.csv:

Refs,Qty,Value,Footprint,LCSC,Notes
R10,1,100k,R_0805_2012Metric,,
"C11,C18,C2,C20,C21,C22,C3,C4,C7,C8,C9,CP1",12,100nF,C_0805_2012Metric,,
"R11,R14,R15,R16,R3,R5,R6,R7",8,10k,R_0805_2012Metric,,
"C10,C5",2,10uF,C_0805_2012Metric,,
"LL1,LL2,LR1,LR2",4,10uH/4A,L_7.3x7.3_H4.5,,
CP2,1,1nF,C_0805_2012Metric,,
"C1,C13,C14,C15,C16,C17,C19",7,1uF,C_0805_2012Metric,,
CF1,1,1uF/63V,C_0805_2012Metric,,
R4,1,2.2k,R_0805_2012Metric,,
C12,1,2.2uF,C_0805_2012Metric,,
"CBL1,CBL2,CBR1,CBR2",4,220nF,C_0805_2012Metric,,
"CI1,CP3",2,220uF/35V,CP_Elec_8x10.5,,
C6,1,22uF,C_0805_2012Metric,,
R8,1,3.3,R_0805_2012Metric,,
CO1,1,330uF/16V,CP_Elec_8x10.5,,
L1,1,33uH/3A,L_12x12mm_H6mm,,
"R12,R13",2,4.7k,R_0805_2012Metric,,
"CB1,CB2",2,470uF/35V,CP_Elec_8x10.5,,
R9,1,5.6k,R_0805_2012Metric,,
U3,1,AMS1117-3.3,SOT-223-3_TabPin2,C6186,SOT-223 LDO
U1,1,CH224K,MSOP-10-1EP_3x3mm_P0.5mm_EP1.73x1.98mm,C970725,"USB-PD sink, ESSOP-10"
R1,1,DNP (NC=20V; 6.8k/24k/56k=9/12/15V),R_0805_2012Metric,,
R17,1,DNP (atten/downmix),R_0805_2012Metric,,
J4,1,ENCODER,JST_PH_B5B-PH-K_1x05_P2.00mm_Vertical,,
U6,1,ESP32-S3 Super Mini,ESP32S3_SuperMini_Socket,,
U7,1,ESP32-S3 Zero,ESP32S3_Zero_Socket,,
U2,1,LM2596S-5.0,TO-263-5_TabPin3,C347421,"fixed 5V buck, TO-263-5"
J3,1,OLED I2C,JST_PH_B4B-PH-K_1x04_P2.00mm_Vertical,,
U4,1,PCM5102A,TSSOP-20_4.4x6.5mm_P0.65mm,C107916,"PCM5102APWR, TSSOP-20"
D2,1,PWR,LED_0805_2012Metric,,
J2,1,SPEAKER,"TerminalBlock_Phoenix_MKDS-1,5-2_1x02_P5.00mm_Horizontal",,
D1,1,SS54,D_SMB,C22452,"5A 40V Schottky, SMB"
U5,1,TPA3116D2,HTSSOP-32-1EP_6.1x11mm_P0.65mm_EP5.2x11mm_Mask4.11x4.36mm_ThermalVias,C51591,"TPA3116D2DADR, HTSSOP-32 PowerPAD"
J1,1,USB-C PD in,USB_C_Receptacle_GCT_USB4085,,"16-pin USB-C receptacle, GCT USB4085 or equiv (power+CC+D)"
